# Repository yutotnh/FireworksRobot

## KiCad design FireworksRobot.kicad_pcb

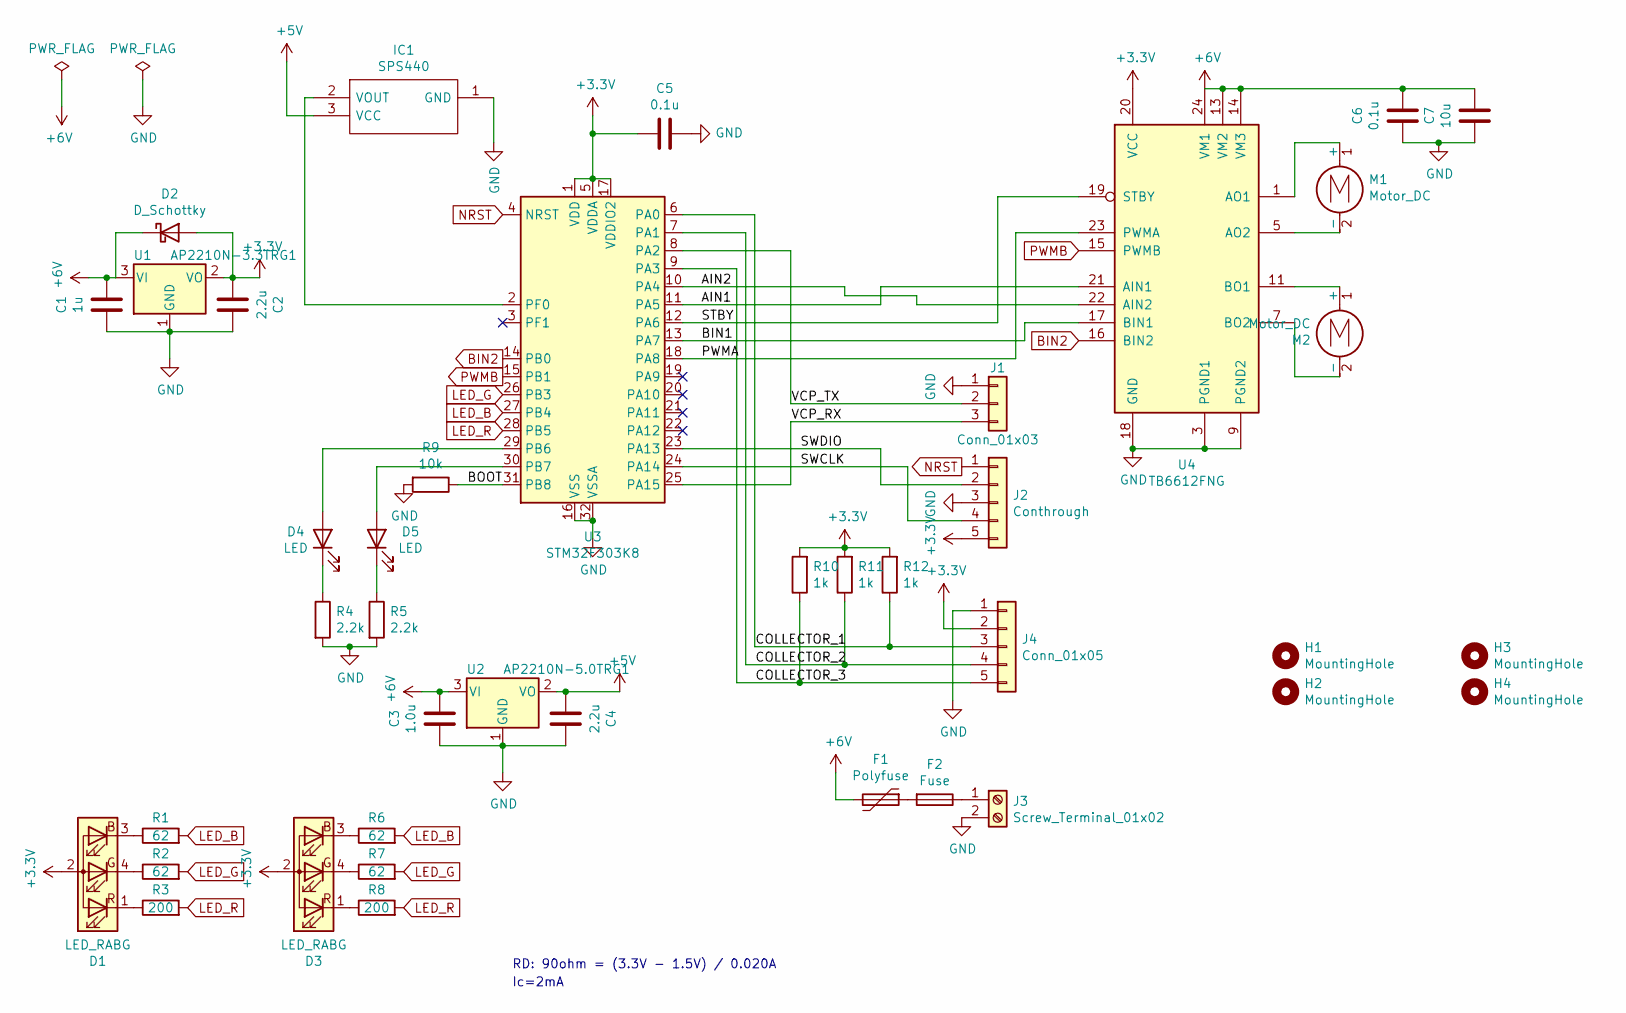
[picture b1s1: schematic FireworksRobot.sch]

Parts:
C1: 1u; C_0805_2012Metric_Pad1.15x1.40mm_HandSolder
C2, C4: 2.2u; C_0805_2012Metric_Pad1.15x1.40mm_HandSolder
C3: 1.0u; C_0805_2012Metric_Pad1.15x1.40mm_HandSolder
C5, C6: 0.1u; C_0805_2012Metric_Pad1.15x1.40mm_HandSolder
C7: 10u; C_0805_2012Metric_Pad1.15x1.40mm_HandSolder
D1, D3: LED_RABG; LED_D5.0mm-4_RGB
D2: D_Schottky; D_0603_1608Metric_Pad1.05x0.95mm_HandSolder
D4, D5: LED; LED_0603_1608Metric_Castellated
F1: Polyfuse; Fuse_Littelfuse_395Series
F2: Fuse; MF505
H1, H2: MountingHole; MountingHole_2.7mm_M2.5
H3, H4: MountingHole; MountingHole_2.2mm_M2
IC1: SPS440
J1: Conn_01x03; Conthrough_1x03_P2.54mm_Vertical
J2: Conthrough; Conthrough_1x05_P2.54mm_Vertical
J3: Screw_Terminal_01x02; TerminalBlock_bornier-2_P5.08mm
J4: Conn_01x05; PinHeader_1x05_P2.54mm_Vertical
M1, M2: Motor_DC; TerminalBlock_bornier-2_P5.08mm
R1, R2, R6, R7: 62; R_0603_1608Metric_Pad1.05x0.95mm_HandSolder
R3, R8: 200; R_0603_1608Metric_Pad1.05x0.95mm_HandSolder
R4, R5: 2.2k; R_0603_1608Metric_Pad1.05x0.95mm_HandSolder
R9: 10k; R_0603_1608Metric_Pad1.05x0.95mm_HandSolder
R10, R11, R12: 1k; R_0603_1608Metric_Pad1.05x0.95mm_HandSolder
U1: AP2210N-3.3TRG1; SOT-23W_Handsoldering
U2: AP2210N-5.0TRG1; SOT-23W_Handsoldering
U3: STM32F303K8; LQFP-32_7x7mm_P0.8mm
U4: TB6612FNG; SSOP-24_5.3x8.2mm_P0.65mm

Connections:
+3V3: C2.2, C5.2, D1.2 (A), D2.2 (A), D3.2 (A), J2.5, J4.2, R10.2, R11.2, R12.2, U1.2 (VO), U3.1 (VDD), U3.5 (VDDA), U3.17 (VDDIO2), U4.20 (VCC)
+5V: C4.2, IC1.3 (VCC), U2.2 (VO)
+6V: C1.1, C3.1, C6.1, C7.1, D2.1 (K), F1.2, U1.3 (VI), U2.3 (VI), U4.13 (VM2), U4.14 (VM3), U4.24 (VM1)
/AIN1: U3.11 (PA5), U4.21 (AIN1)
/AIN2: U3.10 (PA4), U4.22 (AIN2)
/BIN1: U3.13 (PA7), U4.17 (BIN1)
/BOOT: R9.1, U3.31 (PB8)
/COLLECTOR_1: J4.3, R12.1, U3.6 (PA0)
/COLLECTOR_2: J4.4, R11.1, U3.7 (PA1)
/COLLECTOR_3: J4.5, R10.1, U3.9 (PA3)
/PWMA: U3.18 (PA8), U4.23 (PWMA)
/STBY: U3.12 (PA6), U4.19 (STBY)
/SWCLK: J2.4, U3.24 (PA14)
/SWDIO: J2.2, U3.23 (PA13)
/VCP_RX: J1.3, U3.25 (PA15)
/VCP_TX: J1.2, U3.8 (PA2)
BIN2: U3.14 (PB0), U4.16 (BIN2)
GND: C1.2, C2.1, C3.2, C4.1, C5.1, C6.2, C7.2, IC1.1 (GND), IC1.4 (GND), IC1.5 (GND), J1.1, J2.3, J3.2, J4.1, R4.2, R5.2, R9.2, U1.1 (GND), U2.1 (GND), U3.16 (VSS), U3.32 (VSSA), U4.3 (PGND1), U4.4 (PGND1), U4.9 (PGND2), U4.10 (PGND2), U4.18 (GND)
LED_B: R1.2, R6.2, U3.27 (PB4)
LED_G: R2.2, R7.2, U3.26 (PB3)
LED_R: R3.2, R8.2, U3.28 (PB5)
NRST: J2.1, U3.4 (NRST)
unnamed: D1.1 (RK), R3.1
unnamed: D1.3 (BK), R1.1
unnamed: D1.4 (GK), R2.1
unnamed: D3.1 (RK), R8.1
unnamed: D3.3 (BK), R6.1
unnamed: D3.4 (GK), R7.1
unnamed: D4.1 (K), R4.1
unnamed: D4.2 (A), U3.29 (PB6)
unnamed: D5.1 (K), R5.1
unnamed: D5.2 (A), U3.30 (PB7)
unnamed: F1.1, F2.2
unnamed: F2.1, J3.1
unnamed: IC1.2 (VOUT), U3.2 (PF0)
unnamed: M1.1 (+), U4.1 (AO1), U4.2 (AO1)
unnamed: M1.2 (-), U4.5 (AO2), U4.6 (AO2)
unnamed: M2.1 (+), U4.11 (BO1), U4.12 (BO1)
unnamed: M2.2 (-), U4.7 (BO2), U4.8 (BO2)
PWMB: U3.15 (PB1), U4.15 (PWMB)

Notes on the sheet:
Ic=2mA
RD: 90ohm = (3.3V - 1.5V) / 0.020A

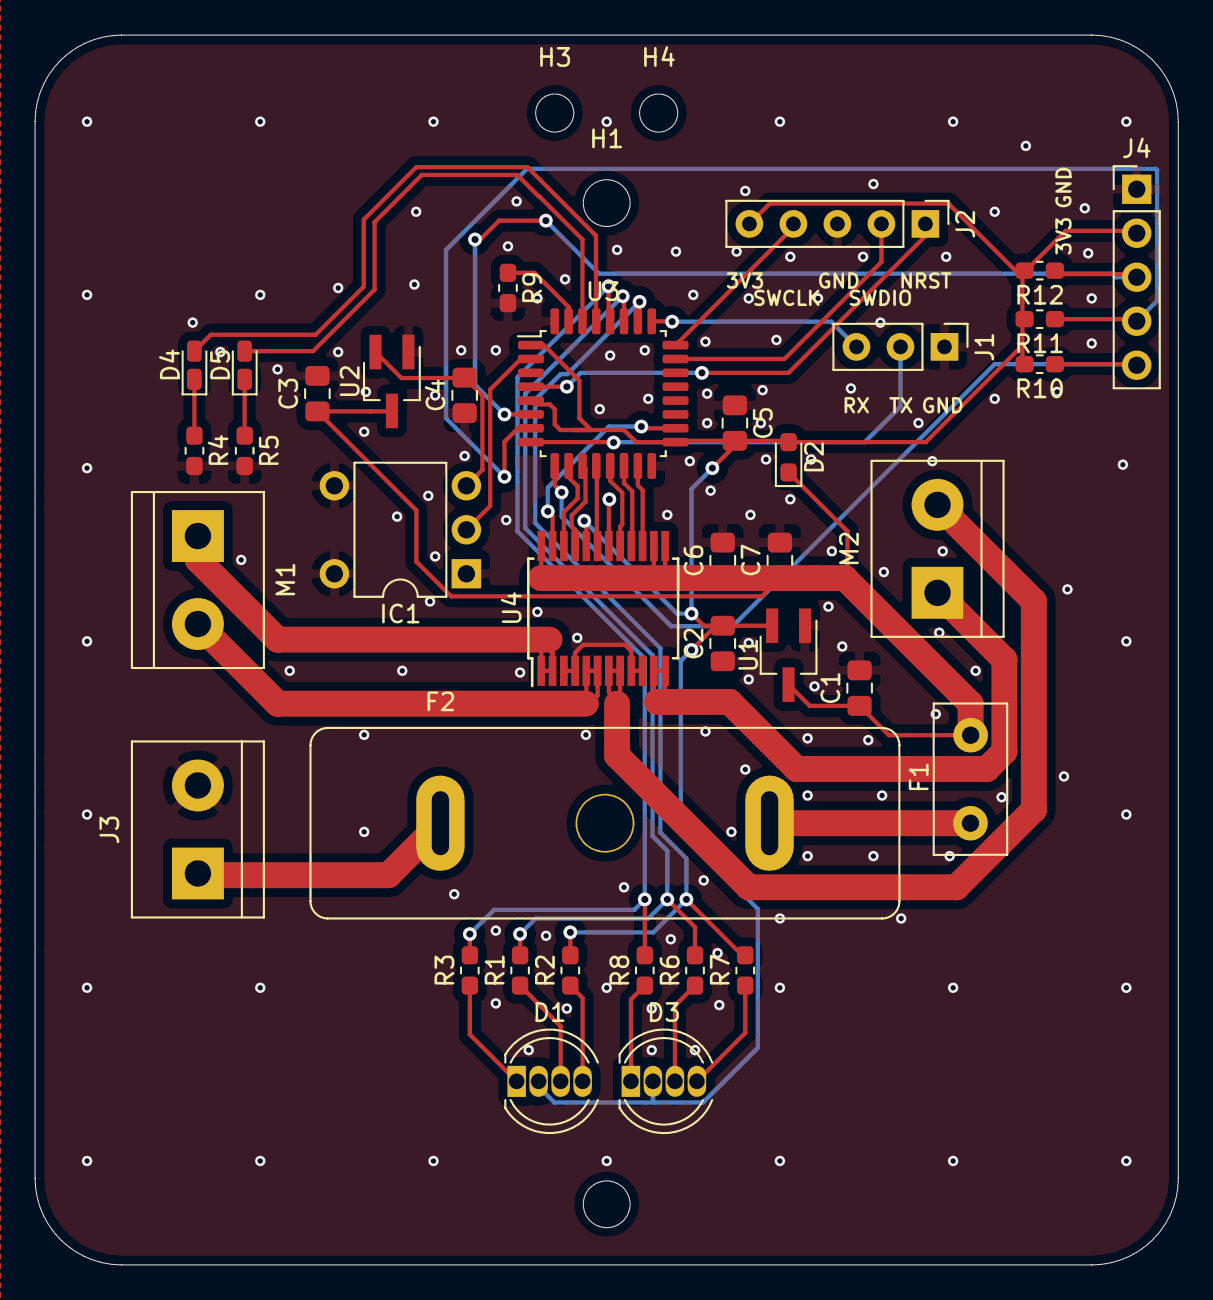
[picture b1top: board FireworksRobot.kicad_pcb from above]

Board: 2 copper layers, 66.0 x 71.0 mm, 41 parts (1 on the bottom side), 40 nets.

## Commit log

2020-07-24 Make Project and Files
2020-09-09 Prototype 1.0
    Elecrowに注文
2020-09-17 order
    order to elecrow
2020-09-30 Update: シンボル
2021-09-26 Create LICENSE
